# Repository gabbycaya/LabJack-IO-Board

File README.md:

# LabJack-IO-Board
- This project is a simple board with I/O components such as pushbuttons, LEDs, and a buzzer for testing the LabJack ports' functions.
- Provides an efficient way of connecting these components to the LabJack.
## How it's Used
The figure below shows a block diagram of how the I/O Device is connected to the LabJack. Please take note of the ports as they are typically labeled according to their function.
- `AO` ports of the board must be connected to `DAC` ports of the LabJack.
- `AI` ports of the board can be connected to any `AIN` ports of the LabJack.
- `PWM` can be connected to any `FIO` ports of the LabJack.

Go to LabJack's [main FAQ page](https://labjack.com/pages/frequently-asked-questions) for more information about DAQ (data acquisition) and how this device works.
## Parts
PCB with enclosure
## Software Used
Autodesk Fusion (for all electronics and 3D models)
## Project Assembly Preview

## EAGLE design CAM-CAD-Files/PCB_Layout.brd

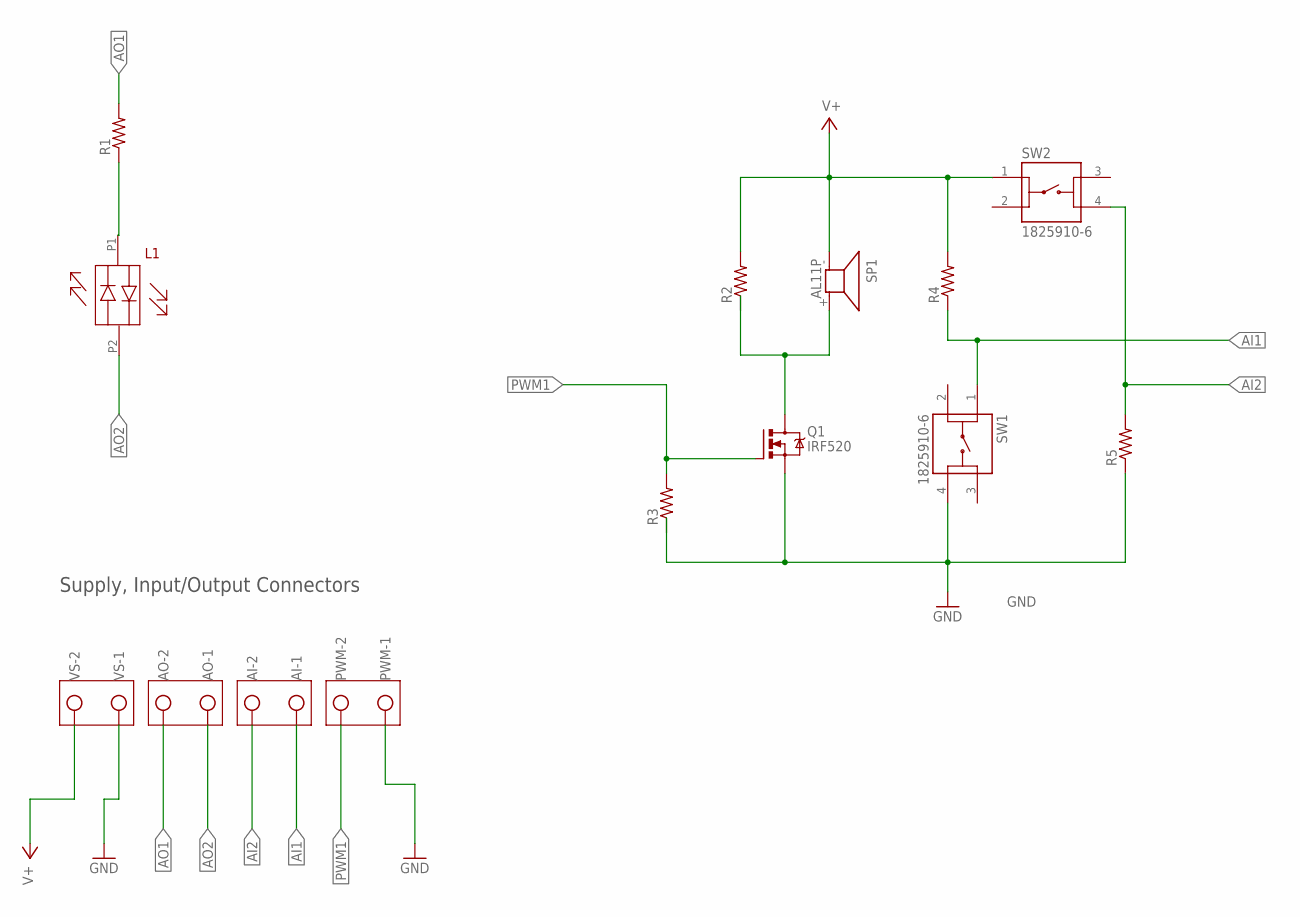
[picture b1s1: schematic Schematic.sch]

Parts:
AI: W237-102
AO: W237-102
PWM: W237-102
Q1: IRF520; TO220BV
R1, R2, R3, R4, R5: R-US_0207/10; 0207/10
SP1: AL11P
SW1, SW2: 1825910-6
U$1: BI-LED
VS: W237-102

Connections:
AI1: AI.1, R4.1, SW1.1
AI2: AI.2, R5.2, SW2.4
AO1: AO.2, R1.2
AO2: AO.1, U$1.P2
GND: PWM.1, Q1.S, R3.1, R5.1, SW1.4, VS.1
unnamed: R1.1, U$1.P1
unnamed: Q1.D, R2.1, SP1.+ (2)
PWM1: PWM.2, Q1.G, R3.2
V+: R2.2, R4.2, SP1.- (1), SW2.1, VS.2

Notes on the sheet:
Supply, Input/Output Connectors

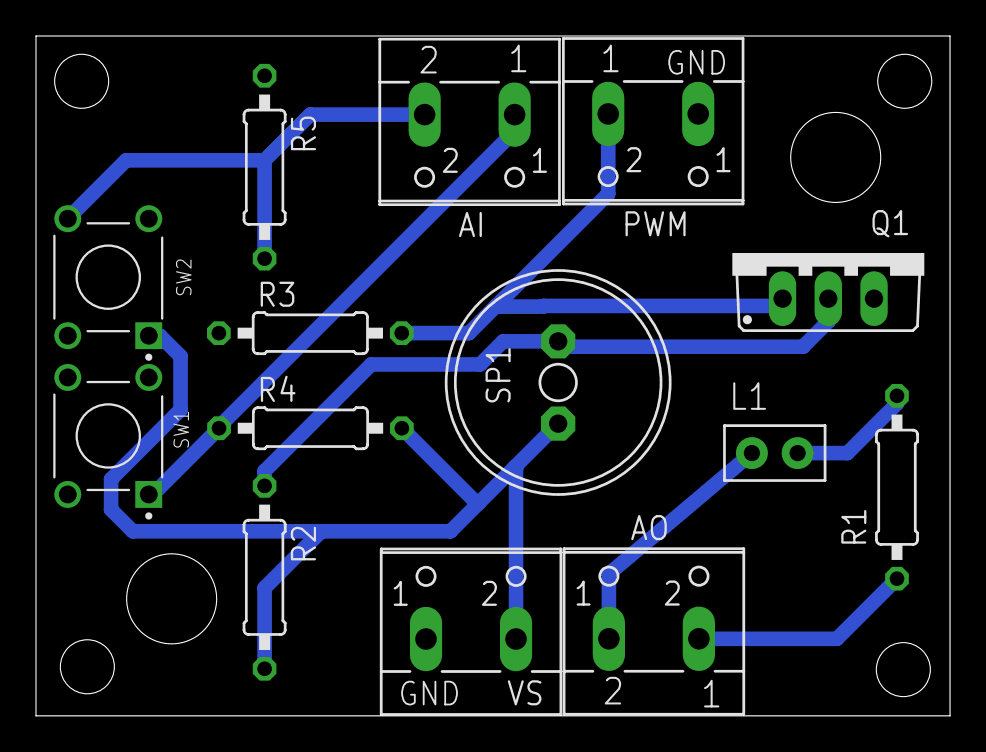
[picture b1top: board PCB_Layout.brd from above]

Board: 2 copper layers, 50.8 x 37.8 mm, 14 parts (0 on the bottom side), 9 nets.
